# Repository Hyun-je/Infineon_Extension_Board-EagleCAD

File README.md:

# Infineon_Extension_Board-EagleCAD

- CAD Version : Eagle CAD 9.6.2 

## PCB Detail
- Dimension : 50.8 mm * 60.96 mm
- Layers : 2
- Base Material : FR-4
- PCB Thickness : 1.6
- Outer Copper Weight : 1 oz
- Surface Finish : HASL (with lead)

|TOP|BOTTOM|
|---|------|
|||

## Parts
- Pin Header 1.27mm SMD (2 x 40) : 1 EA
- Pin Header 2.54mm Through Hole (2 x 10) : 4 EA

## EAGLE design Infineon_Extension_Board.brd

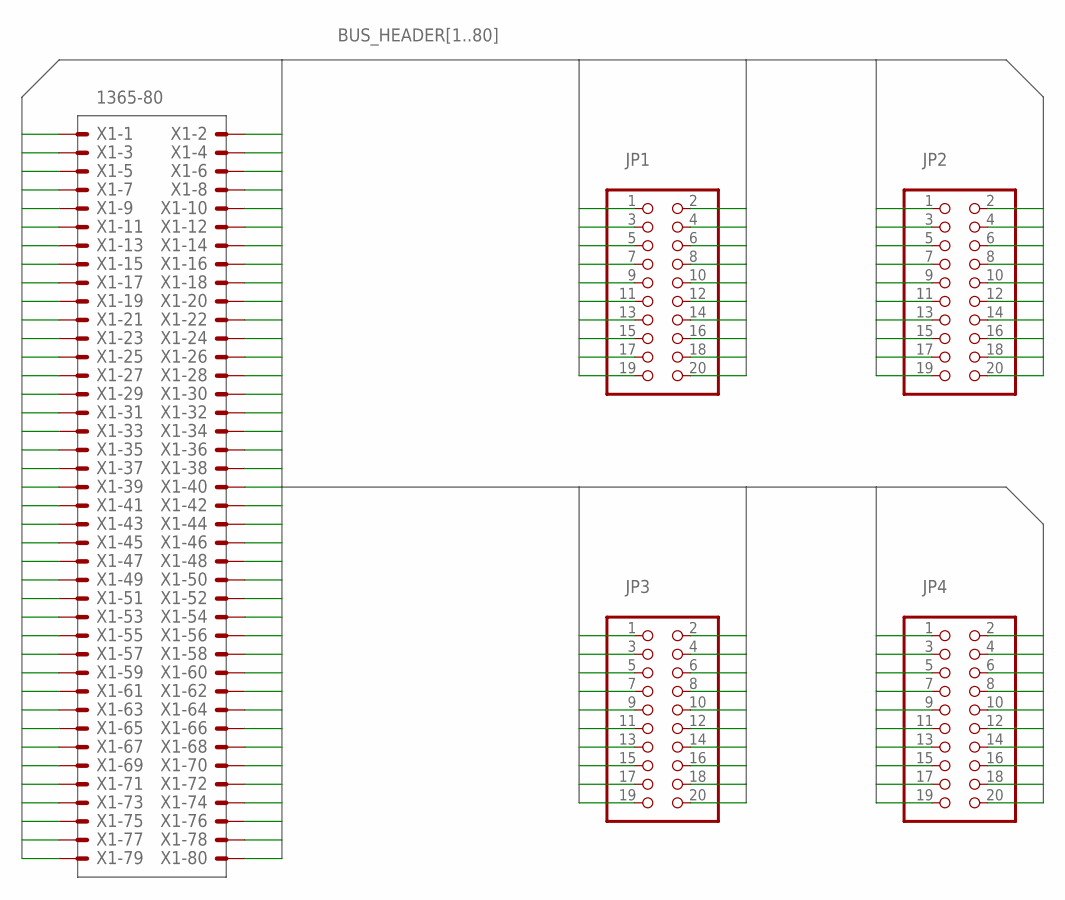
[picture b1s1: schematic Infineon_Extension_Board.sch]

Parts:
JP1, JP2, JP3, JP4: PINHD-2X10; 2X10
X1: 1365-80

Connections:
BUS_HEADER1: JP1.1, X1.1
BUS_HEADER2: JP1.2, X1.2
BUS_HEADER3: JP1.3, X1.3
BUS_HEADER4: JP1.4, X1.4
BUS_HEADER5: JP1.5, X1.5
BUS_HEADER6: JP1.6, X1.6
BUS_HEADER7: JP1.7, X1.7
BUS_HEADER8: JP1.8, X1.8
BUS_HEADER9: JP1.9, X1.9
BUS_HEADER10: JP1.10, X1.10
BUS_HEADER11: JP1.11, X1.11
BUS_HEADER12: JP1.12, X1.12
BUS_HEADER13: JP1.13, X1.13
BUS_HEADER14: JP1.14, X1.14
BUS_HEADER15: JP1.15, X1.15
BUS_HEADER16: JP1.16, X1.16
BUS_HEADER17: JP1.17, X1.17
BUS_HEADER18: JP1.18, X1.18
BUS_HEADER19: JP1.19, X1.19
BUS_HEADER20: JP1.20, X1.20
BUS_HEADER21: JP2.1, X1.21
BUS_HEADER22: JP2.2, X1.22
BUS_HEADER23: JP2.3, X1.23
BUS_HEADER24: JP2.4, X1.24
BUS_HEADER25: JP2.5, X1.25
BUS_HEADER26: JP2.6, X1.26
BUS_HEADER27: JP2.7, X1.27
BUS_HEADER28: JP2.8, X1.28
BUS_HEADER29: JP2.9, X1.29
BUS_HEADER30: JP2.10, X1.30
BUS_HEADER31: JP2.11, X1.31
BUS_HEADER32: JP2.12, X1.32
BUS_HEADER33: JP2.13, X1.33
BUS_HEADER34: JP2.14, X1.34
BUS_HEADER35: JP2.15, X1.35
BUS_HEADER36: JP2.16, X1.36
BUS_HEADER37: JP2.17, X1.37
BUS_HEADER38: JP2.18, X1.38
BUS_HEADER39: JP2.19, X1.39
BUS_HEADER40: JP2.20, X1.40
BUS_HEADER41: JP3.1, X1.41
BUS_HEADER42: JP3.2, X1.42
BUS_HEADER43: JP3.3, X1.43
BUS_HEADER44: JP3.4, X1.44
BUS_HEADER45: JP3.5, X1.45
BUS_HEADER46: JP3.6, X1.46
BUS_HEADER47: JP3.7, X1.47
BUS_HEADER48: JP3.8, X1.48
BUS_HEADER49: JP3.9, X1.49
BUS_HEADER50: JP3.10, X1.50
BUS_HEADER51: JP3.11, X1.51
BUS_HEADER52: JP3.12, X1.52
BUS_HEADER53: JP3.13, X1.53
BUS_HEADER54: JP3.14, X1.54
BUS_HEADER55: JP3.15, X1.55
BUS_HEADER56: JP3.16, X1.56
BUS_HEADER57: JP3.17, X1.57
BUS_HEADER58: JP3.18, X1.58
BUS_HEADER59: JP3.19, X1.59
BUS_HEADER60: JP3.20, X1.60
BUS_HEADER61: JP4.1, X1.61
BUS_HEADER62: JP4.2, X1.62
BUS_HEADER63: JP4.3, X1.63
BUS_HEADER64: JP4.4, X1.64
BUS_HEADER65: JP4.5, X1.65
BUS_HEADER66: JP4.6, X1.66
BUS_HEADER67: JP4.7, X1.67
BUS_HEADER68: JP4.8, X1.68
BUS_HEADER69: JP4.9, X1.69
BUS_HEADER70: JP4.10, X1.70
BUS_HEADER71: JP4.11, X1.71
BUS_HEADER72: JP4.12, X1.72
BUS_HEADER73: JP4.13, X1.73
BUS_HEADER74: JP4.14, X1.74
BUS_HEADER75: JP4.15, X1.75
BUS_HEADER76: JP4.16, X1.76
BUS_HEADER77: JP4.17, X1.77
BUS_HEADER78: JP4.18, X1.78
BUS_HEADER79: JP4.19, X1.79
BUS_HEADER80: JP4.20, X1.80

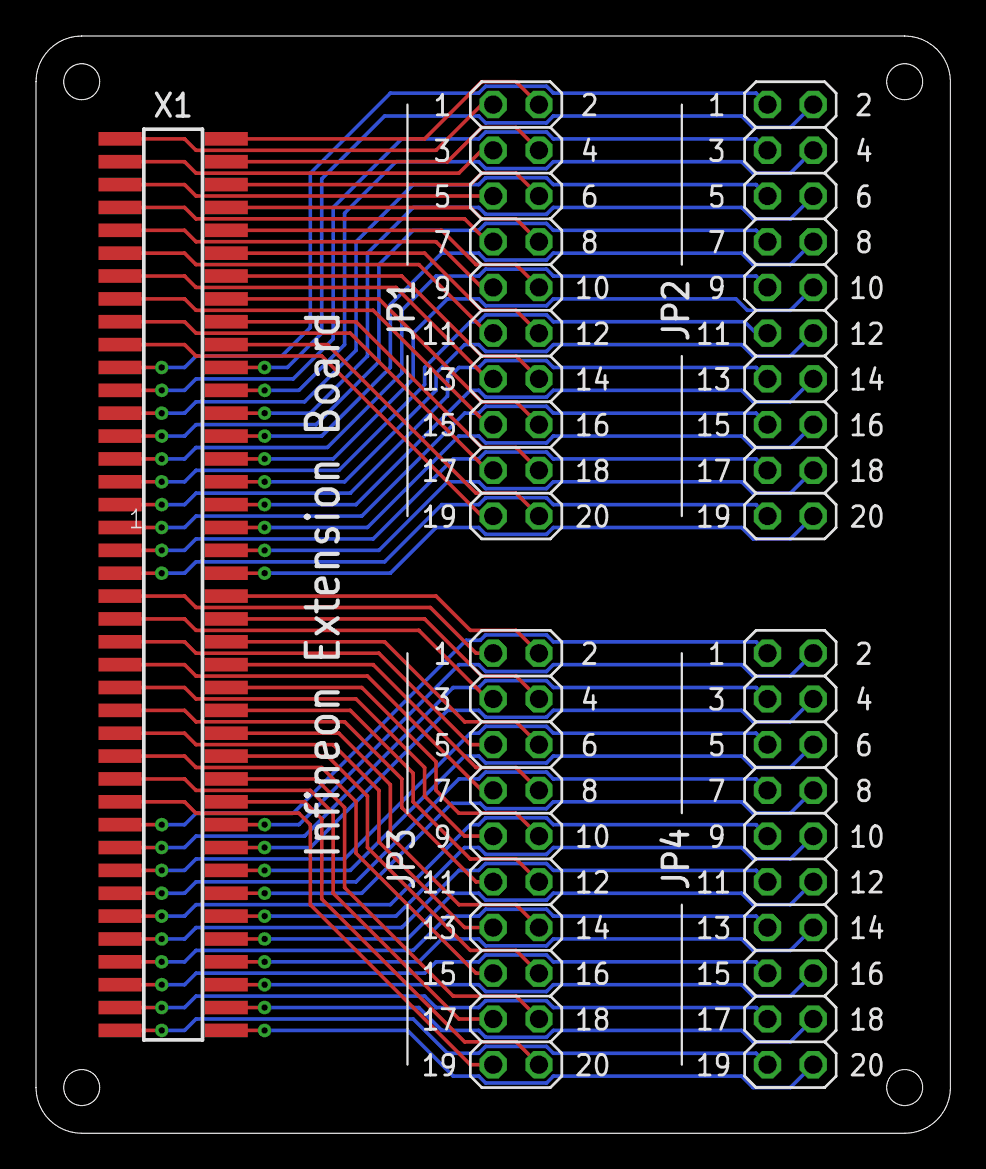
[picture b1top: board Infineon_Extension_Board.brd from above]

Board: 2 copper layers, 50.8 x 61.0 mm, 5 parts (0 on the bottom side), 80 nets.

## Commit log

2022-06-30 Add CAD files
2022-06-30 Add Gerber
